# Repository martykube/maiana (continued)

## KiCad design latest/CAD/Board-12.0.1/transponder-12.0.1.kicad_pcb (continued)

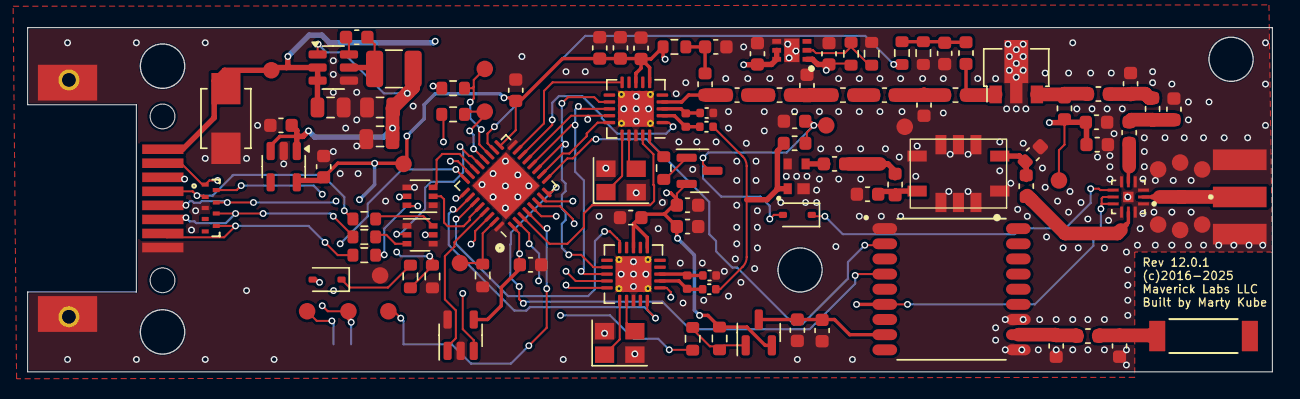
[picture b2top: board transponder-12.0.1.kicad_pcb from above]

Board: 4 copper layers, 90.4 x 25.0 mm, 115 parts (1 on the bottom side), 81 nets.

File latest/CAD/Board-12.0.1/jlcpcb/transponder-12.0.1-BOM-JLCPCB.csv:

Comment,Designator,Footprint,LCSC
1575AT43A0040001E,AE1,ANT_1575AT_JOT,
91pF,C2,C_0603_1608Metric,C701317
36pF,C15,C_0603_1608Metric,C134070
2.2nF,C16,C_0603_1608Metric,C77033
20pF,C21,C_0603_1608Metric,C77030
16pF,C22,C_0603_1608Metric,C327125
10uF,C29,C_0805_2012Metric,C18185759
4pF,C32,C_0603_1608Metric,C437534
2.2pF,C33,C_0603_1608Metric,C282246
2pF,"C1,C37",C_0603_1608Metric,C81437
470pF,"C13,C18,C20",C_0603_1608Metric,C85979
110pF,"C14,C17",C_0603_1608Metric,C327208
22nF,"C19,C31",C_0603_1608Metric,C106222
22uF,"C28,C38",C_0805_2012Metric,C20416420
"0.1uF,0.1uf","C3,C9,C11,C27,C34,C35",C_0603_1608Metric,C14663
7.5pF,"C4,C36",C_0402_1005Metric,C88938
13pF,"C5,C6",C_0402_1005Metric,C130119
2.2uF,"C7,C10,C23,C24,C25,C26,C30,C39",C_0603_1608Metric,C380321
100pF,"C8,C12",C_0603_1608Metric,C71664
D3V3X8U9LP3810-7,CR1,U-DFN3810-9TYPE_B_DIO,C1973794
SMBJ16CA,D1,DIOM4336X265N,C113990
BAT54WS,"D3,D4",D_SOD-323,C124205
LDFPVR,IC1,SON65P200X200X100-7N-D,C2969978
CON-SMA-EDGE-S,J3,RFSOLUTIONS_CON-SMA-EDGE-S,
RJ-82A86MMNL,J4,RJ-82A86MMNL,C7205195
2.2uH AFL160808-2R2MLH,L4,L_0603_1608Metric,C55265173
13nH,L5,L_0603_1608Metric,C701184
39nH,L6,L_0603_1608Metric,C86134
20nH,L7,L_0603_1608Metric,C77124
47nH,L10,L_0603_1608Metric,C98076
68nH,L11,L_0603_1608Metric,C86135
22uH,L12,L_1210_3225Metric,C307600
5.6nH,L14,L_0603_1608Metric,C98081
470nH,"L1,L8,L9",L_0603_1608Metric,C113132
180nH,"L15,L16",L_0603_1608Metric,C98091
200nH,"L2,L3",L_0402_1005Metric,C2045944
AFT05MS004NT1,Q1,SOT-89-3,C713822
AO3401A,"Q2,Q7",SOT-23,C15127
3k3,R3,R_0603_1608Metric,C22978
22R,R4,R_0603_1608Metric,C23345
1k1,"R1,R17,R18",R_0603_1608Metric,C22764
100R,"R12,R13,R14,R15,R16",R_0603_1608Metric,C22775
10k,"R2,R6,R10,R11",R_0603_1608Metric,C25804
47k,"R5,R9",R_0603_1608Metric,C25819
PSA4-5043+,U3,PSA4-5043_,C5240848
L76L-M33,U4,XCVR_L76L-M33,C2916232
STM32L412KBU6,U5,QFN-32-1EP_5x5mm_P0.5mm_EP3.45x3.45mm,C529439
AP63205WU,U6,TSOT-23-6,C2071056
24LC01BT/OT,U7,SOT-23-5,C511269
SKY13330-397LF,U8,QFN50P200X200X65-13N,C2654715
TB0436A,U11,TB0436A,
NCP163ASN330T1G,U12,SOT-23-5,C603656
Si4460,"U1,U2",QFN-20-1EP_4x4mm_P0.5mm_EP2.6x2.6mm_ThermalVias,C2151590
DMN63D8LDW-7,"U9,U10",SOT-363_SC-70-6,C211422
ECS-300-10-33B-CKM-TR,"Y1,Y2",Crystal_SMD_3225-4Pin_3.2x2.5mm,

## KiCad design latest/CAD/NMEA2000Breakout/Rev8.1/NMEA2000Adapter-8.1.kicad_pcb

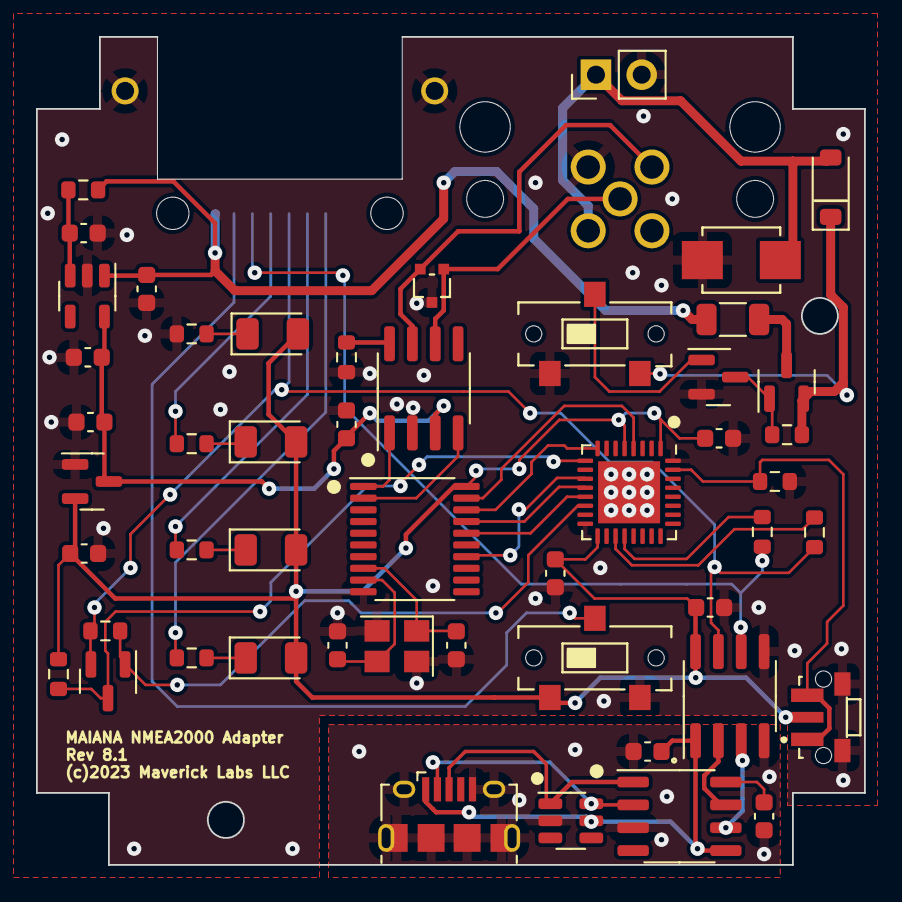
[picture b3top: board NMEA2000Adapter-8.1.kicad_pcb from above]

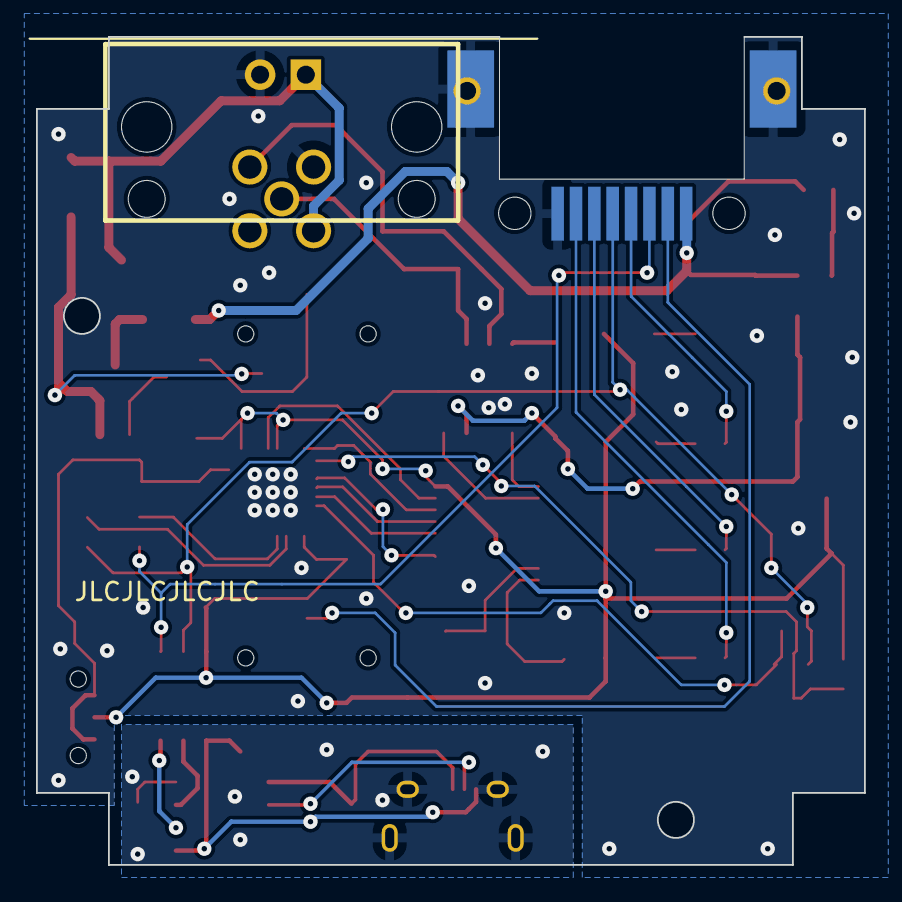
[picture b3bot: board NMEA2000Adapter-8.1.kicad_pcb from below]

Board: 2 copper layers, 46.0 x 46.0 mm, 52 parts (2 on the bottom side), 44 nets.

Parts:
C1, C2, C3, C11, C12, C13: 0.1uF; C_0603_1608Metric
C4, C5: 20pF; C_0603_1608Metric
C6, C7, C8, C9, C10: 1uF; C_0603_1608Metric
D1, D2, D3, D4: LED; LED_1206_3216Metric
D5: PESD1CAN-UX; SOT323
D6: SMBJ16CA; DIOM4336X265N
D8: B5819W; D_SOD-123
J1: 12-3701-05; MICRO_C_5PIN
J2: RJ-82A86MMNL
J3: USB_B_Micro; USB_Micro-B_Amphenol_10118194_Horizontal
J4: Conn_01x02; PinHeader_1x02_P2.54mm_Vertical
Q1, Q3: BSS138; SOT-23
Q2: AO3401A; SOT-23
R1, R2, R3, R4: 2k2; R_0603_1608Metric
R5, R6, R7, R8, R9, R10: 10k; R_0603_1608Metric
R11, R12: 0R; R_0603_1608Metric
SW1, SW2: CL-SB-12B-01; CL-SB-12B-01T
SW3: TS-1814; TE_1977066-1
TH1: BSMD1206-050-16V; R_1206_3216Metric
U1: STM32L432KBUx; QFN-32-1EP_5x5mm_P0.5mm_EP3.45x3.45mm
U2: MCP2515-xST; TSSOP-20_4.4x6.5mm_P0.65mm
U3: MCP2551-I-SN; SOIC-8_3.9x4.9mm_P1.27mm
U4: SRV05-4; SOT-23-6
U5: CH340N; SO-8_3.9x4.9mm_P1.27mm
U6: ISO7721DR; SOIC-8_3.9x4.9mm_P1.27mm
U7: TJ5205SF5-5.0; SOT-23-5
U8: SE8533X2-HF; SOT-23
Y1: X322516MOB4SI; Crystal_SMD_3225-4Pin_3.2x2.5mm

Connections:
+3.3V: C2.1, C10.1, C12.1, C13.1, D1.2 (A), D2.2 (A), D3.2 (A), D4.2 (A), R10.1, SW2.1, SW3.2, U1.1 (VDD), U1.5 (VDDA), U1.17 (VDD), U2.20 (VDD), U6.8 (VDD2), U8.2 (VO)
+5V: C8.1, C9.1, C11.1, U3.3 (VDD), U7.5 (OUT), U8.3 (VI)
+12V: D6.2, D8.2 (A), J1.2, J4.1
/CAN/CAN_H: D5.2, J1.4, U3.7 (CANH)
/CAN/CAN_L: D5.1, J1.5, U3.6 (CANL)
/CAN/NRST: U1.4 (NRST), U2.19 (~RESET)
/CAN/SPI_CS: U1.8 (PA2), U2.18 (~CS)
/CAN/SPI_MISO: U1.12 (PA6), U2.17 (SO)
/CAN/SPI_MOSI: U1.13 (PA7), U2.16 (SI)
/CAN/SPI_SCK: U1.11 (PA5), U2.14 (SCK)
/Connections/AIS_RX_EVENT: J2.P$6 (6), R3.2
/Connections/AIS_TX_EVENT: J2.P$7 (7), R4.2
/Connections/GPS_STATUS: J2.P$4 (4), R2.2
/Connections/MCU_UART_RX: R12.2, U1.20 (PA10)
/Connections/MCU_UART_TX: R11.2, U1.19 (PA9)
/Connections/TRANSPONDER_UART_TX: J2.P$5 (5), Q3.2 (S), R9.2, R11.1, U6.7 (VIA)
/Connections/TX_DISABLE: J2.P$2 (2), SW2.C
/Connections/V_OUT: C7.1, J2.P$1 (1), R6.1, TH1.1, U7.1 (IN)
/MCU/BOOT0: R8.1, SW3.1, SW3.3, U1.31 (PH3)
/Power/PWR_CTRL: Q1.1 (G), SW1.C
/Power/V_IN: D8.1 (K), Q2.2 (S), R5.1, SW1.3
CH340_RX: U5.7 (RX), U6.2 (VOA)
CH340_TX: U5.6 (TX), U6.3 (VIB)
D+: J3.3 (D+), U4.1 (IO1), U5.1 (D+)
D-: J3.2 (D-), U4.6 (IO4), U5.2 (D-)
GND: C2.2, C4.2, C5.2, C6.2, C7.2, C8.2, C9.2, C10.2, C11.2, C12.2, C13.2, D5.3, D6.1, J1.3, J2.P$8 (8), J2.P$9, J2.P$10, J2.P$11, J2.P$12, J4.2, Q1.2 (S), R1.2, R7.2, R8.2, SW1.1, SW2.3, SW3.S1 (SHIELD), SW3.S2 (SHIELD), U1.16 (VSS), U1.32 (VSS), U1.33 (VSS), U2.10 (VSS), U3.2 (VSS), U6.5 (GND2), U7.2 (GND), U8.1 (GND), Y1.2, Y1.4
GND2: C1.2, C3.2, J3.5 (GND), J3.6 (Shield), U4.2 (VN), U5.3 (GND), U6.4 (GND1)
NMEA_RX: Q3.3 (D), R10.2, U1.9 (PA3)
NMEA_RX_EN: Q3.1 (G), R9.1, U1.14 (PB0)
unnamed: D1.1 (K), R1.1
unnamed: D2.1 (K), R2.1
unnamed: D3.1 (K), R3.1
unnamed: D4.1 (K), R4.1
unnamed: Q1.3 (D), Q2.1 (G), R5.2
unnamed: Q2.3 (D), TH1.2
unnamed: U2.2 (RXCAN), U3.4 (RXD)
unnamed: U2.1 (TXCAN), U3.1 (TXD)
unnamed: R7.1, U3.8 (Rs)
unnamed: C1.1, U5.8 (V3)
unnamed: C6.1, R6.2, U7.3 (EN)
TRANSPONDER_UART_RX: J2.P$3 (3), R12.1, U6.6 (VOB)
VBUS: C3.1, J3.1 (VBUS), U4.5 (VP), U5.5 (VCC), U6.1 (VDD1)
XTL1: C5.1, U2.8 (OSC2), Y1.1
XTL2: C4.1, U2.9 (OSC1), Y1.3

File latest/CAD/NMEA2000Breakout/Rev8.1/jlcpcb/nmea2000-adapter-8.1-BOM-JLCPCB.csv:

Comment,Designator,Footprint,LCSC Part #
0.1uF 50V X7R,"C1,C2,C3,C11,C12,C13",0603,C1591
20pF 50V C0G,"C4,C5",0603,C91702
1uF 50V X5R,"C6,C7,C8,C9,C10",0603,C15849
LED green,"D1,D2,D3,D4",1206,C14641
PESD1CAN-UX,D5,SOT-323,C152727
SMBJ16CA,D6,SMB,C113990
B5819W SL,D8,SOD-123,C8598
RJ45 FG RJ-055-1,J2,RJ-82A86MMNL,C7205195
10118194-0001LF,J3,USB_Micro-B,C132563
BSS138LT1G,"Q1,Q3",SOT-23,C82045
AO3401A,Q2,SOT-23,C15127
2.2k,"R1,R2,R3,R4",0603,C4190
10k,"R5,R6,R7,R8,R9,R10",0603,C25804
0R,"R11,R12",0603,C21189
CL-SB-12B-01,"SW1,SW2",CL-SB-12B-01T,C5619703
1977066-1,SW3,TE_1977066-1,C2972219
BSMD1206-050-16V,TH1,1206,C883124
STM32L432KBU6,U1,QFN-32,C94784
MCP2515-I/ST,U2,TSSOP-20,C15193
MCP2551-I/SN,U3,SOIC-8,C7376
SRV05-4,U4,SOT-23-6,C2836319
CH340N,U5,SO-8,C2977777
ISO7721DR,U6,SOIC-8,C366164
TJ5205SF5-5.0,U7,SOT-23-5,C126091
SE8533X2-HF,U8,SOT-23,C115016
X322516MOB4SI 16MHz,Y1,3225,C12668
